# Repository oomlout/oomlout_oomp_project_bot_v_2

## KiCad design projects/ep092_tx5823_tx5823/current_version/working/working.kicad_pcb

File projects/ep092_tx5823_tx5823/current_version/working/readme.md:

# tx5823
 
## summary 
* id: ep092_tx5823_tx5823
* user: ep092
* name: tx5823
* board: tx5823
* repo: https://github.com/ep092/TX5823
* src_file_repo_kicad_pcb: TX5823.kicad_pcb
* src_file_repo_kicad_pcb_link: https://github.com/ep092/TX5823/tree/master/TX5823.kicad_pcb

* src_file_repo_sch: TX5823.sch
* src_file_repo_sch_link: https://github.com/ep092/TX5823/tree/master/TX5823.sch
* full details link: https://github.com/oomlout/oomlout_oomp_project_bot_v_2/tree/main/projects/ep092_tx5823_tx5823/current_version/working

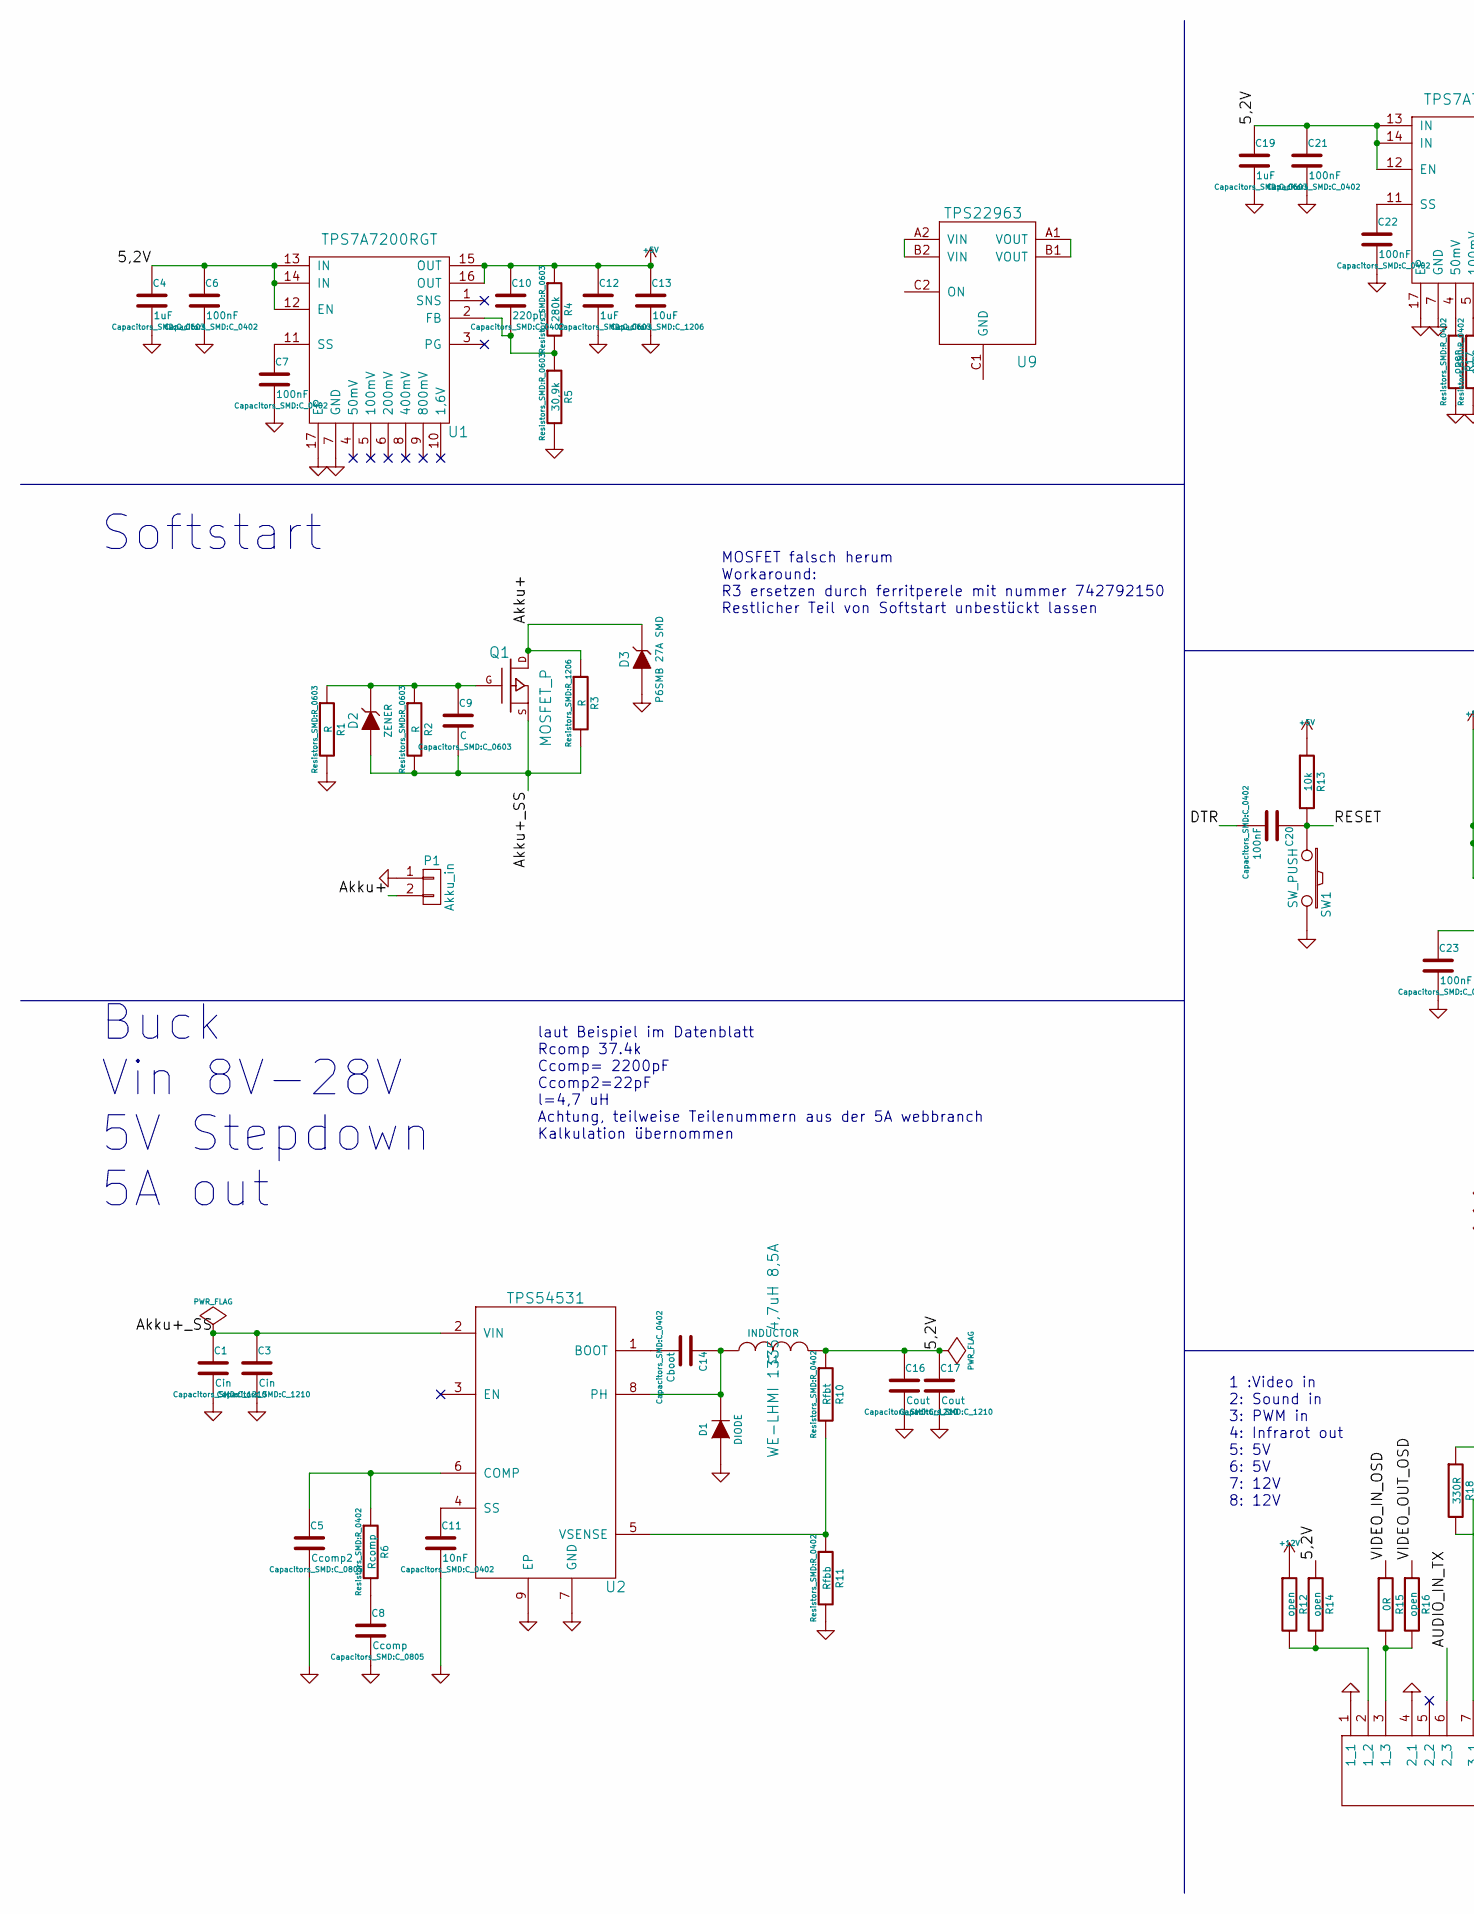
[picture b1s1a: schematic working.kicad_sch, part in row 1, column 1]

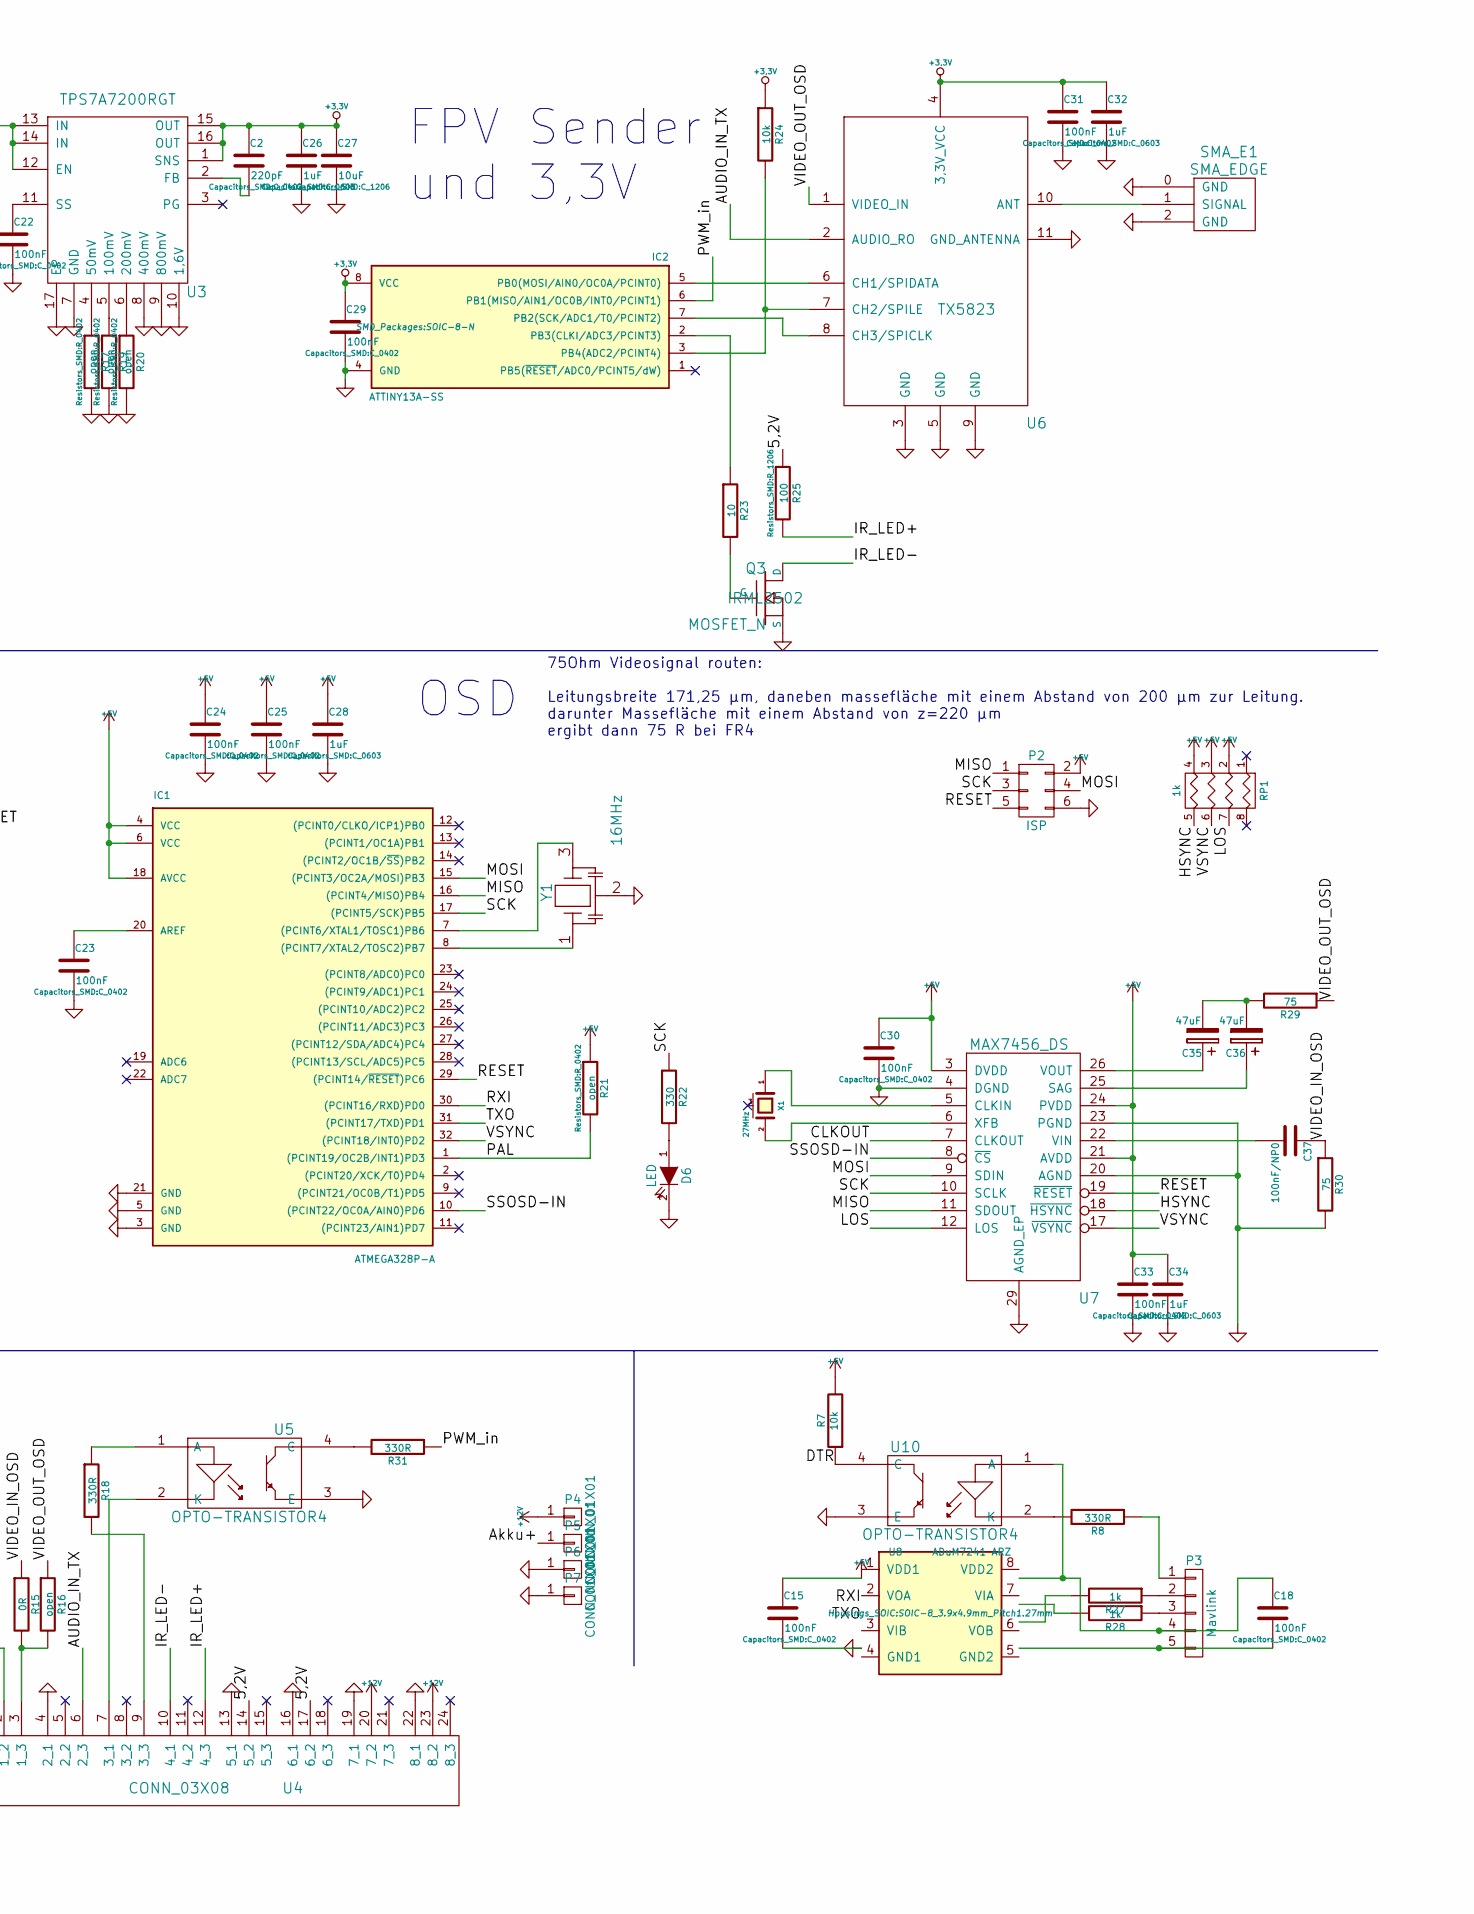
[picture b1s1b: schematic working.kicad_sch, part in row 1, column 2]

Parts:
C1, C3: Cin; C_1210
C2, C10: 220pF; C_0402
C4, C12, C19, C26, C28, C32, C34: 1uF; C_0603
C5: Ccomp2; C_0805
C6, C7, C15, C18, C20, C21, C22, C23, C24, C25, C29, C30, C31, C33: 100nF; C_0402
C8: Ccomp; C_0805
C9: C; C_0603
C11: 10nF; C_0402
C13, C27: 10uF; C_1206
C14: Cboot; C_0402
C16, C17: Cout; C_1210
C35, C36: 47uF; TantalC_SizeB_EIA-3528_Reflow
C37: 100nF/NP0; C_1206
D1: DIODE; POWERDI5
D2: ZENER; Diode-MiniMELF_Standard
D3: P6SMB 27A SMD; Diode-SMB_Standard
D6: LED; LED-0603
IC1: ATMEGA328P-A; TQFP-32_7x7mm_Pitch0.8mm
IC2: ATTINY13A-SS; SOIC-8-N
L1: INDUCTOR; Choke_SMD_Wuerth-WE-PD-Typ-LS_Handsoldering
P1: Akku_in; Socket_Strip_Angled_1x02
P2: ISP; micro_match3x2
P3: Mavlink; Connector_Molex_PicoBlade_53261-0571
P4, P5, P6, P7: CONN_01X01; Pin_Header_Straight_1x01
Q1: MOSFET_P; SO8_WITH_EP
Q3: MOSFET_N; SOT23_GDS
R1, R2: R; R_0603
R3: R; R_1206
R4: 280k; R_0603
R5: 30,9k; R_0603
R6: Rcomp; R_0402
R7, R13, R24: 10k; R_0603
R8: 330R; R_0603
R10: Rfbt; R_0402
R11: Rfbb; R_0402
R12, R14, R16: open; R_0603
R15: 0R; R_0603
R17, R19, R20, R21: open; R_0402
R18: 330R; R_0805
R22: 330; R_0805
R23: 10; R_0805
R25: 100; R_1206
R27, R28: 1k; R_0603
R29, R30: 75; C_0805
R31: 330R; C_0805
RP1: 1k; R_Array_Concave_4x0603
SMA_E1: SMA_EDGE
SW1: SW_PUSH; EVQP7A
U1, U3: TPS7A7200RGT; QFN-16-1EP_3x3mm_Pitch0.5mm
U2: TPS54531; SO8_EP
U4: CONN_03X08; Conn_03x08
U5, U10: OPTO-TRANSISTOR4; SO-4
U6: TX5823
U7: MAX7456_DS; TSSOP-28_4.4x9.7mm_Pitch0.65mm_EP
U8: ADuM7241 ARZ; SOIC-8_3.9x4.9mm_Pitch1.27mm
U9: TPS22963; DSBGS(6)
X1: 27MHz; CRYSTAL_MT
Y1: 16MHz; CerOsc_3,2x1,3

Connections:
+3.3V: C2.1, C26.1, C27.1, C29.1, C31.1, C32.1, IC2.8 (VCC), R24.1, U3.1 (SNS), U3.15 (OUT), U3.16 (OUT), U6.4 (3,3V_VCC)
+5V: C10.1, C12.1, C13.1, C15.1, C24.1, C25.1, C28.1, C30.1, C33.1, C34.1, IC1.4 (VCC), IC1.6 (VCC), IC1.18 (AVCC), P2.2, R4.1, R7.2, R13.1, R21.1, RP1.2, RP1.3, RP1.4, U1.15 (OUT), U1.16 (OUT), U7.3 (DVDD), U7.21 (AVDD), U7.24 (PVDD), U8.1 (VDD1)
+12V: P4.1, R12.1, U4.20 (7_2), U4.23 (8_2)
/5,2V: C4.1, C6.1, C16.1, C17.1, C19.1, C21.1, L1.2, R10.1, R14.1, R25.1, U1.12 (EN), U1.13 (IN), U1.14 (IN), U3.12 (EN), U3.13 (IN), U3.14 (IN), U4.14 (5_2), U4.17 (6_2)
/AUDIO_IN_TX: U4.6 (2_3), U6.2 (AUDIO_RO)
/Akku+: D3.2 (K), P1.2, P5.1, Q1.D, R3.1
/Akku+_SS: C1.1, C3.1, C9.2, D2.1 (A), Q1.S, R2.2, R3.2, U2.2 (VIN)
/CLKOUT: U7.7 (CLKOUT)
/DTR: C20.2, R7.1, U10.4 (C)
/HSYNC: RP1.5 (R4), U7.18 (~HSYNC)
/IR_LED+: R25.2, U4.12 (4_3)
/IR_LED-: Q3.D, U4.10 (4_1)
/LOS: RP1.7 (R2), U7.12 (LOS)
/MISO: IC1.16 ((PCINT4/MISO)PB4), P2.1, U7.11 (SDOUT)
/MOSI: IC1.15 ((PCINT3/OC2A/MOSI)PB3), P2.4, U7.9 (SDIN)
/PAL: IC1.1 ((PCINT19/OC2B/INT1)PD3), R21.2
/PWM_in: IC2.6 (PB1(MISO/AIN1/OC0B/INT0/PCINT1)), R31.1
/RESET: C20.1, IC1.29 ((PCINT14/~RESET)PC6), P2.5, R13.2, SW1.1, U7.19 (~RESET)
/RXI: IC1.30 ((PCINT16/RXD)PD0), U8.2 (VOA)
/SCK: IC1.17 ((PCINT5/SCK)PB5), P2.3, R22.1, U7.10 (SCLK)
/SSOSD-IN: IC1.10 ((PCINT22/OC0A/AIN0)PD6), U7.8 (~CS)
/TXO: IC1.31 ((PCINT17/TXD)PD1), U8.3 (VIB)
/VIDEO_IN_OSD: C37.1, R15.1, R30.1
/VIDEO_OUT_OSD: R16.1, R29.1, U6.1 (VIDEO_IN)
/VSYNC: IC1.32 ((PCINT18/INT0)PD2), RP1.6 (R3), U7.17 (~VSYNC)
GND: C1.2, C3.2, C4.2, C5.2, C6.2, C7.2, C8.2, C11.2, C12.2, C13.2, C15.2, C16.2, C17.2, C19.2, C21.2, C22.2, C23.2, C24.2, C25.2, C26.2, C27.2, C28.2, C29.2, C30.2, C31.2, C32.2, C33.2, C34.2, D1.1 (A), D3.1 (A), D6.2 (K), IC1.3 (GND), IC1.5 (GND), IC1.21 (GND), IC2.4 (GND), P1.1, P2.6, P6.1, P7.1, Q3.S, R1.2, R5.2, R11.2, R17.2, R19.2, R20.2, R30.2, SMA_E1.0 (GND), SMA_E1.2 (GND), SW1.2, U1.7 (GND), U1.17 (EP), U2.7 (GND), U2.9 (EP), U3.7 (GND), U3.8 (400mV), U3.9 (800mV), U3.10 (1,6V), U3.17 (EP), U4.1 (1_1), U4.4 (2_1), U4.13 (5_1), U4.16 (6_1), U4.19 (7_1), U4.22 (8_1), U5.3 (E), U6.3 (GND), U6.5 (GND), U6.9 (GND), U6.11 (GND_ANTENNA), U7.4 (DGND), U7.20 (AGND), U7.23 (PGND), U7.29 (AGND_EP), U8.4 (GND1), U10.3 (E), Y1.2
unnamed: C2.2, U3.2 (FB)
unnamed: C5.1, R6.1, U2.6 (COMP)
unnamed: C7.1, U1.11 (SS)
unnamed: C8.1, R6.2
unnamed: C9.1, D2.2 (K), Q1.G, R1.1, R2.1
unnamed: C10.2, R4.2, R5.1, U1.2 (FB)
unnamed: C11.1, U2.4 (SS)
unnamed: C14.1, D1.2 (K), L1.1, U2.8 (PH)
unnamed: C14.2, U2.1 (BOOT)
unnamed: C22.1, U3.11 (SS)
unnamed: C23.1, IC1.20 (AREF)
unnamed: C35.1, U7.26 (VOUT)
unnamed: C35.2, C36.2, R29.2
unnamed: C36.1, U7.25 (SAG)
unnamed: C37.2, U7.22 (VIN)
unnamed: D6.1 (A), R22.2
unnamed: IC1.7 ((PCINT6/XTAL1/TOSC1)PB6), Y1.3
unnamed: IC1.8 ((PCINT7/XTAL2/TOSC2)PB7), Y1.1
unnamed: IC2.2 (PB3(CLKI/ADC3/PCINT3)), R23.1
unnamed: IC2.3 (PB4(ADC2/PCINT4)), R24.2, U6.7 (CH2/SPILE)
unnamed: IC2.5 (PB0(MOSI/AIN0/OC0A/PCINT0)), U6.6 (CH1/SPIDATA)
unnamed: IC2.7 (PB2(SCK/ADC1/T0/PCINT2)), U6.8 (CH3/SPICLK)
unnamed: P3.1, R8.1
unnamed: P3.2, R27.1
unnamed: P3.3, R28.1
unnamed: Q3.G, R23.2
unnamed: R8.2, U10.2 (K)
unnamed: R10.2, R11.1, U2.5 (VSENSE)
unnamed: R12.2, R14.2, U4.2 (1_2)
unnamed: R15.2, R16.2, U4.3 (1_3)
unnamed: R17.1, U3.4 (50mV)
unnamed: R18.1, U5.1 (A)
unnamed: R18.2, U4.9 (3_3)
unnamed: R19.1, U3.5 (100mV)
unnamed: R20.1, U3.6 (200mV)
unnamed: R27.2, U8.6 (VOB)
unnamed: R28.2, U8.7 (VIA)
unnamed: R31.2, U5.4 (C)
unnamed: SMA_E1.1 (SIGNAL), U6.10 (ANT)
unnamed: U4.7 (3_1), U5.2 (K)
unnamed: U7.5 (CLKIN), X1.1
unnamed: U7.6 (XFB), X1.2
unnamed: U9.A1 (VOUT), U9.B1 (VOUT)
unnamed: U9.A2 (VIN), U9.B2 (VIN)

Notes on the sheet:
OSD
Buck Vin 8V-28V 5V Stepdown 5A out
1 :Video in 2: Sound in 3: PWM in 4: Infrarot out 5: 5V 6: 5V 7: 12V 8: 12V
FPV Sender und 3,3V
laut Beispiel im Datenblatt Rcomp 37.4k Ccomp= 2200pF Ccomp2=22pF l=4,7 uH Achtung, teilweise Teilenummern aus der 5A webbranch Kalkulation übernommen
MOSFET falsch herum Workaround: R3 ersetzen durch ferritperele mit nummer 742792150 Restlicher Teil von Softstart unbestückt lassen
Softstart
75Ohm Videosignal routen: Leitungsbreite 171,25 µm, daneben massefläche mit einem Abstand von 200 µm zur Leitung. darunter Massefläche mit einem Abstand von z=220 µm ergibt dann 75 R bei FR4

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
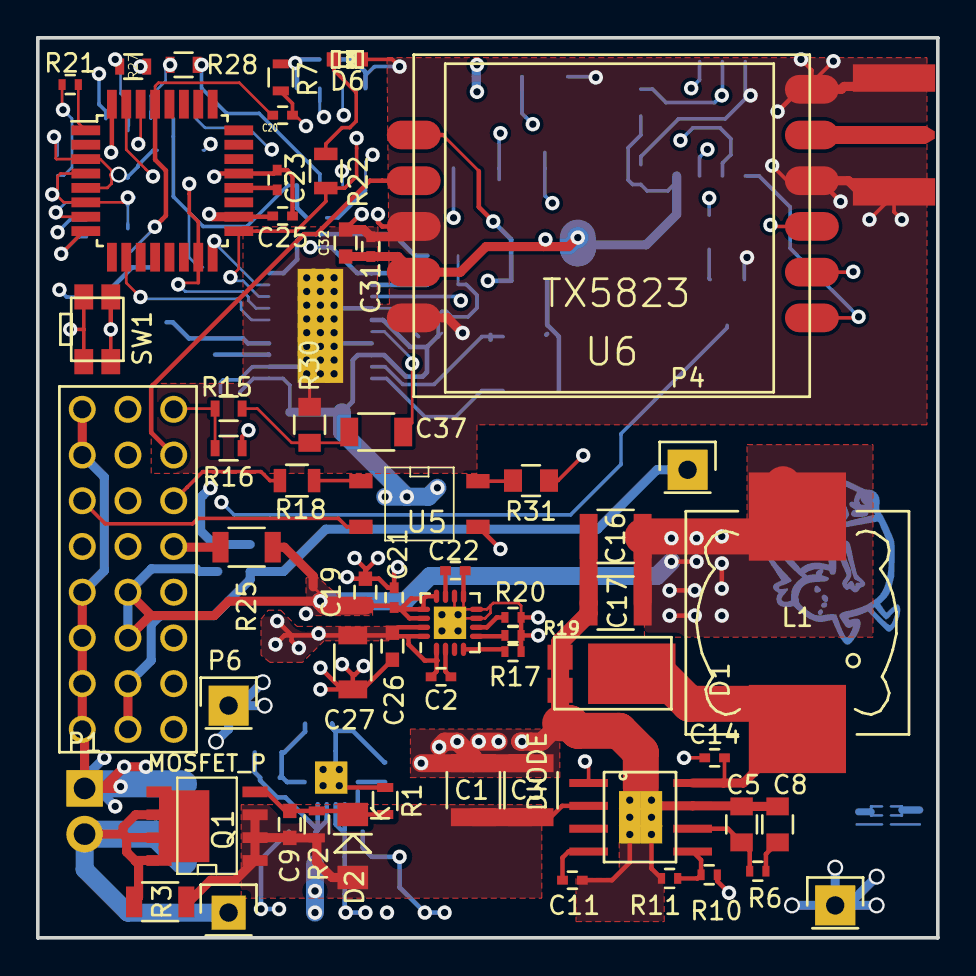
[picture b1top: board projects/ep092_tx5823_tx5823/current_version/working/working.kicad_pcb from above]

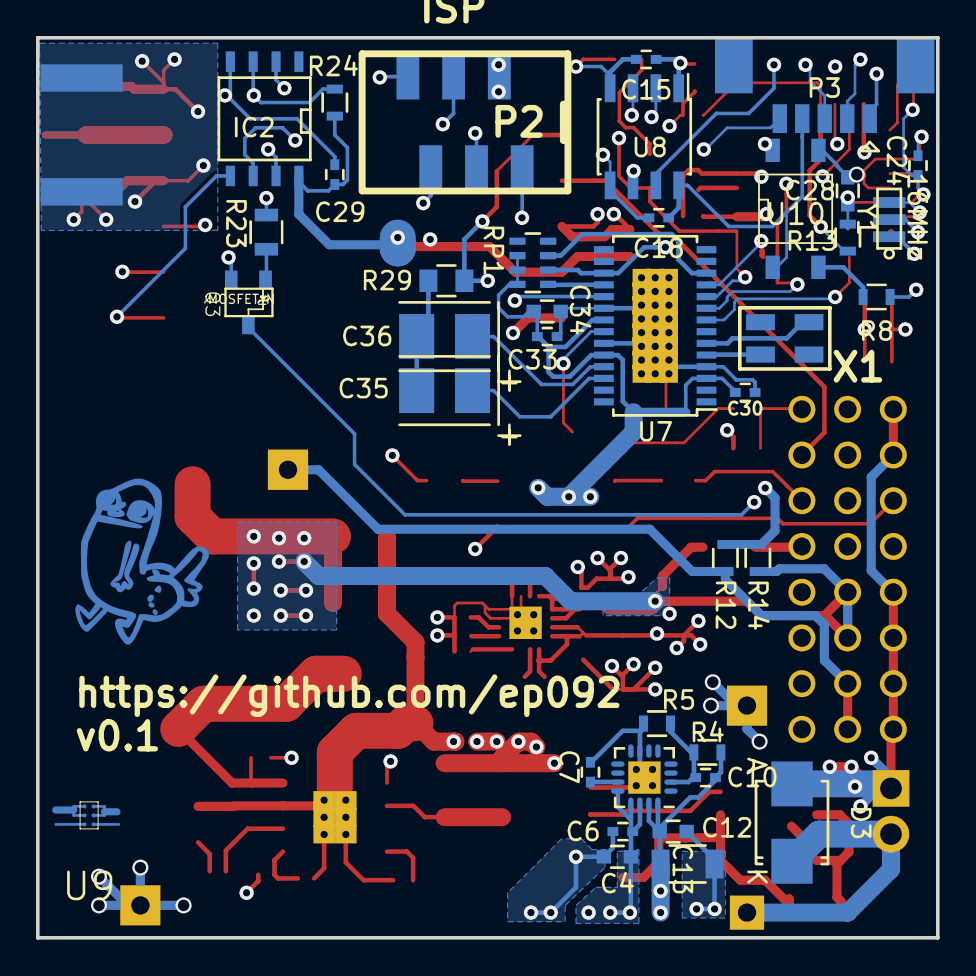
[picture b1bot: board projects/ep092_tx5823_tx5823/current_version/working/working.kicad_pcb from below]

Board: 4 copper layers, 50.0 x 50.0 mm, 97 parts (38 on the bottom side), 71 nets.

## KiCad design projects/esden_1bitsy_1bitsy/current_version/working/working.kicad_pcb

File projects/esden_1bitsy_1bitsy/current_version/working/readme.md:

# 1bitsy
 
## summary 
* id: esden_1bitsy_1bitsy
* user: esden
* name: 1bitsy
* board: 1bitsy
* repo: https://github.com/esden/1BitSy
* src_file_repo_kicad_pcb: 1bitsy/v1.0d/1bitsy-rr.kicad_pcb
* src_file_repo_kicad_pcb_link: https://github.com/esden/1BitSy/tree/master/1bitsy/v1.0d/1bitsy-rr.kicad_pcb

* src_file_repo_sch: 1bitsy/v1.0c/1bitsy.sch
* src_file_repo_sch_link: https://github.com/esden/1BitSy/tree/master/1bitsy/v1.0c/1bitsy.sch
* full details link: https://github.com/oomlout/oomlout_oomp_project_bot_v_2/tree/main/projects/esden_1bitsy_1bitsy/current_version/working

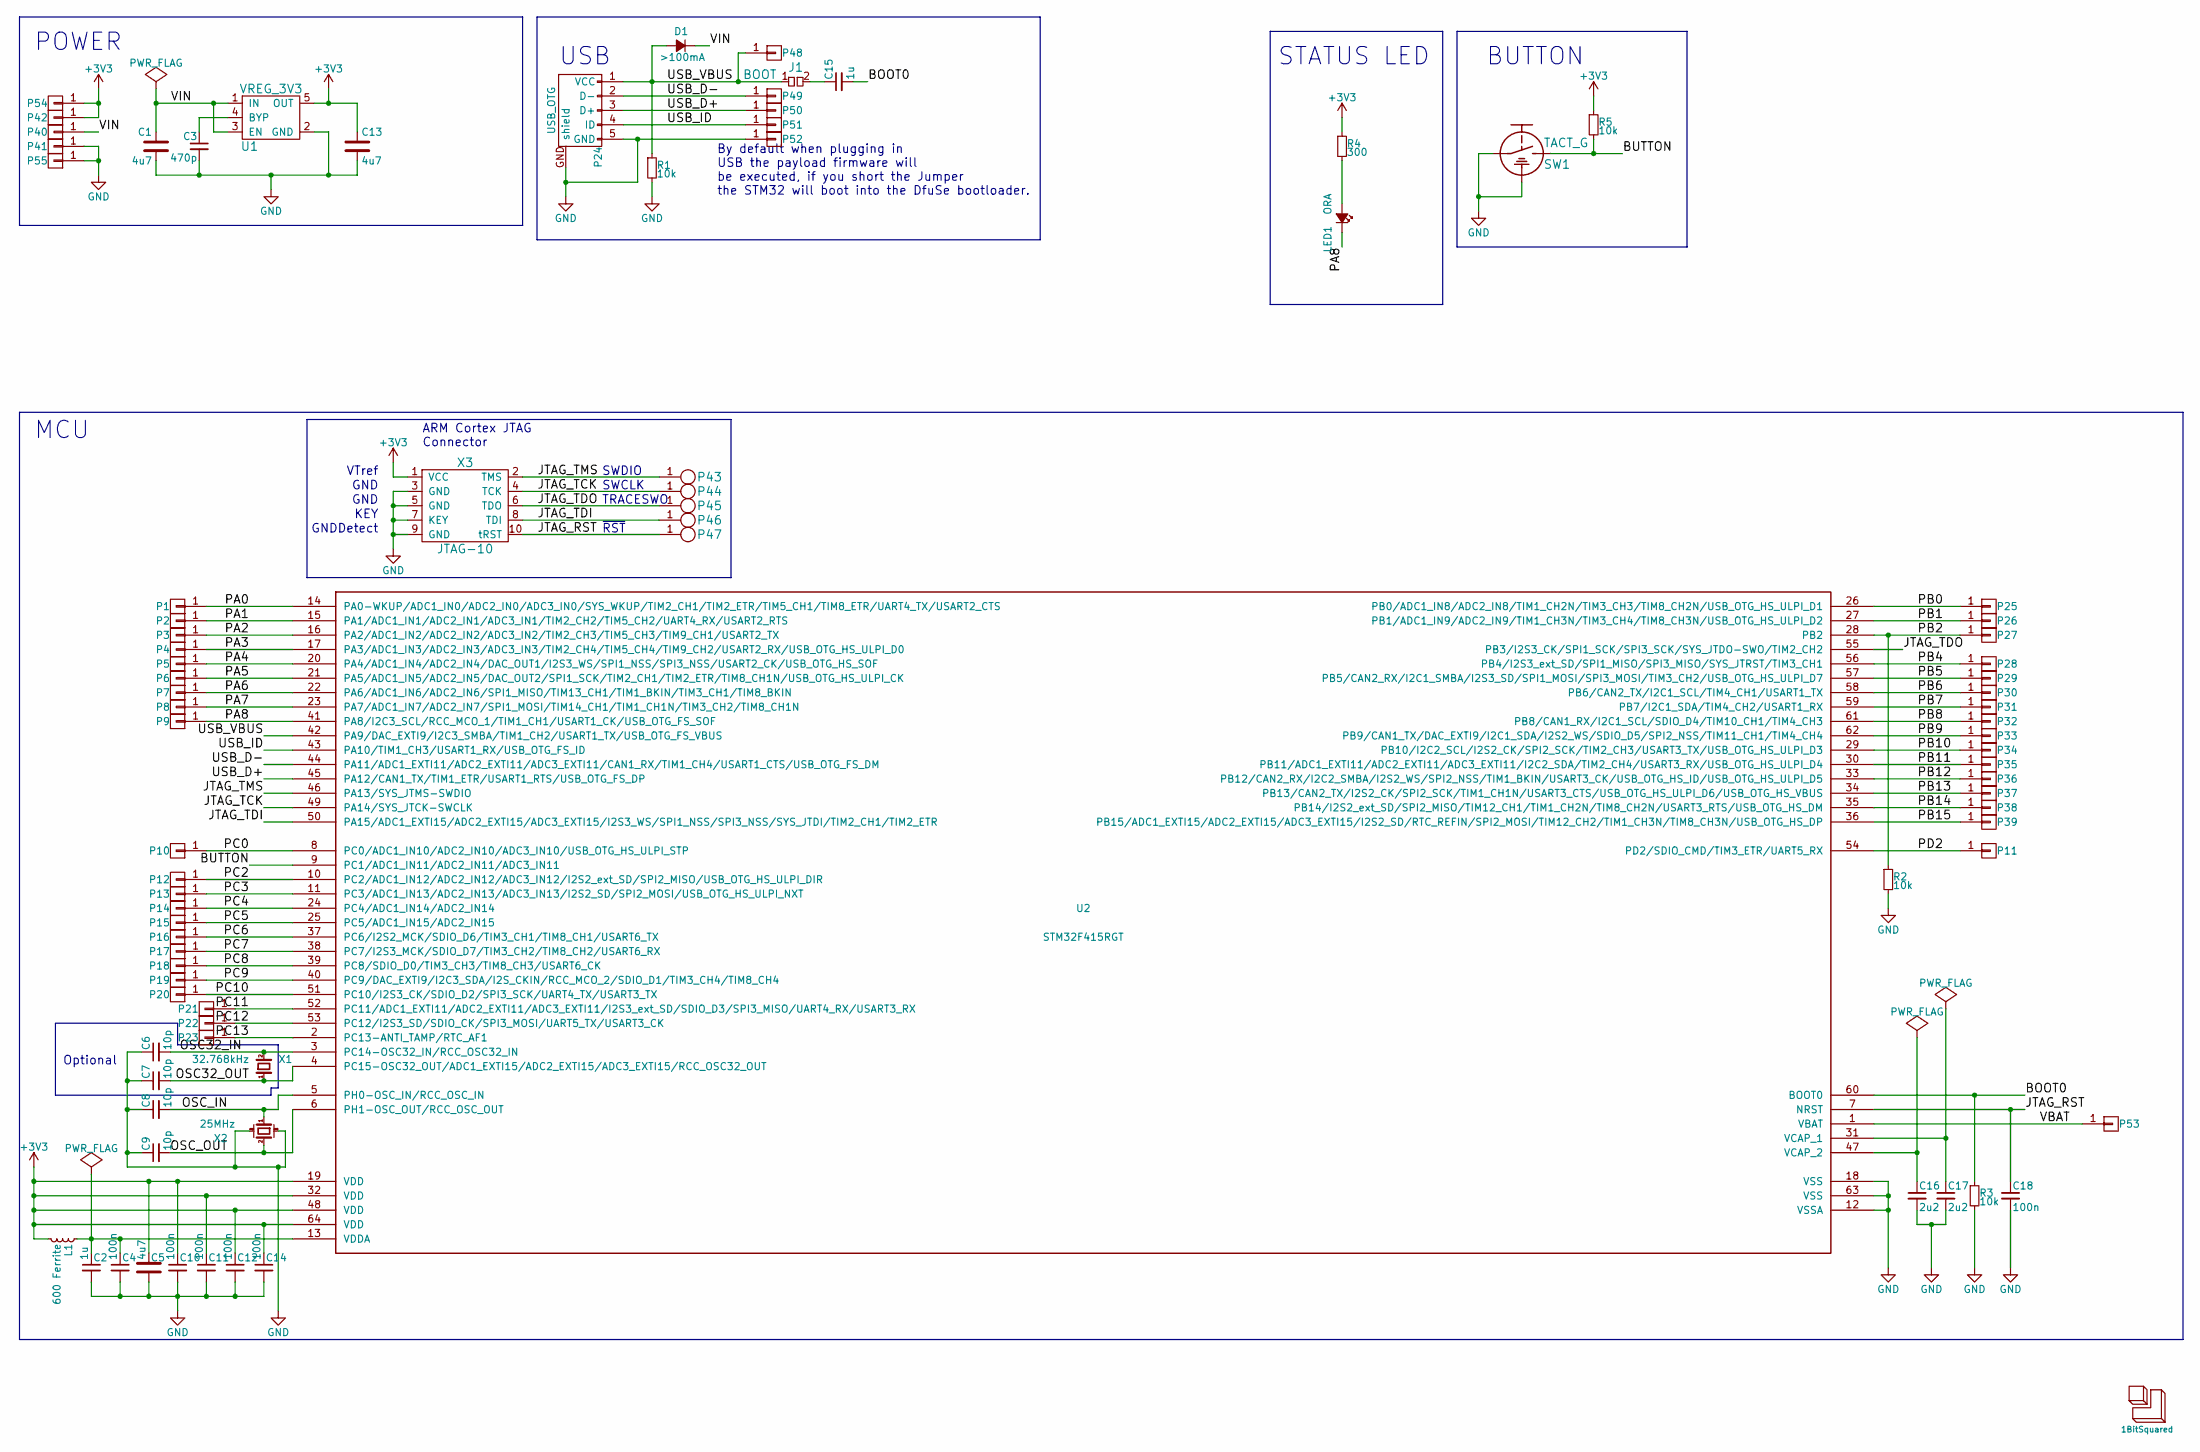
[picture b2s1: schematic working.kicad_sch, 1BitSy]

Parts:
C1, C5, C13: 4u7; C_0603
C2, C15: 1u; C_0402
C3: 470p; C_0402
C4, C10, C11, C12, C14, C18: 100n; C_0402
C6, C7: 10p; C_0603
C8, C9: 10p; C_0402
C16, C17: 2u2; C_0402
D1: >100mA; D_0603
J1: BOOT; J_0603
L1: 600 Ferrite; L_0402
LED1: ORA; D_0603
LOGO1: 1BitSquared; 1b2_Logo_SilkS_7.5mm
P1, P2, P3, P4, P5, P6, P7, P8, P9, P10, P11, P12, P13, P14, P15, P16, P17, P18, P19, P20, P21, P22, P23, P25, P26, P27, P28, P29, P30, P31, P32, P33, P34, P35, P36, P37, P38, P39, P40, P41, P42, P53, P54, P55: CONN_01X01; Pin_Header_Straight_Round_1x01
P24: USB_OTG; Connector_USB_Micro_B_SMD
P43, P44, P45, P46, P47: TP; POGO_PAD_SMD_R_1x1
P48, P49, P50, P51, P52: CONN_01X01; PAD_SMD_1x2.65
R1, R2, R3, R5: 10k; R_0402
R4: 300; R_0402
SW1: TACT_G; Tact_Switch_Top_B3U-1000P
U1: VREG_3V3; SOT-23-5
U2: STM32F415RGT; LQFP-64_10x10mm_Pitch0.5mm
X1: 32.768kHz; ABS07
X2: 25MHz; ABM8
X3: JTAG-10; FTSH-105-XX-X-DV

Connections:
+3V3: C5.1, C10.1, C11.1, C12.1, C13.1, C14.1, L1.1, P42.1, P54.1, R4.1, R5.1, U1.5 (OUT), U2.19 (VDD), U2.32 (VDD), U2.48 (VDD), U2.64 (VDD), X3.1 (VCC)
/BOOT0: C15.2, R3.1, U2.60 (BOOT0)
/BUTTON: R5.2, SW1.2, U2.9 (PC1/ADC1_IN11/ADC2_IN11/ADC3_IN11)
/JTAG_RST: C18.1, P47.1, U2.7 (NRST), X3.10 (tRST)
/JTAG_TCK: P44.1, U2.49 (PA14/SYS_JTCK-SWCLK), X3.4 (TCK)
/JTAG_TDI: P46.1, U2.50 (PA15/ADC1_EXTI15/ADC2_EXTI15/ADC3_EXTI1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), X3.8 (TDI)
/JTAG_TDO: P45.1, U2.55 (PB3/I2S3_CK/SPI1_SCK/SPI3_SCK/SYS_JTDO-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), X3.6 (TDO)
/JTAG_TMS: P43.1, U2.46 (PA13/SYS_JTMS-SWDIO), X3.2 (TMS)
/OSC32_IN: C6.2, U2.3 (PC14-OSC32_IN/RCC_OSC32_IN), X1.2
/OSC32_OUT: C7.2, U2.4 (PC15-OSC32_OUT/ADC1_EXTI15/ADC2_EXTI15/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), X1.1
/OSC_IN: C8.2, U2.5 (PH0-OSC_IN/RCC_OSC_IN), X2.1
/OSC_OUT: C9.2, U2.6 (PH1-OSC_OUT/RCC_OSC_OUT), X2.2
/PA0: P1.1, U2.14 (PA0-WKUP/ADC1_IN0/ADC2_IN0/ADC3_IN0/SYS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)
/PA1: P2.1, U2.15 (PA1/ADC1_IN1/ADC2_IN1/ADC3_IN1/TIM2_CH2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)
/PA2: P3.1, U2.16 (PA2/ADC1_IN2/ADC2_IN2/ADC3_IN2/TIM2_CH3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)
/PA3: P4.1, U2.17 (PA3/ADC1_IN3/ADC2_IN3/ADC3_IN3/TIM2_CH4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)
/PA4: P5.1, U2.20 (PA4/ADC1_IN4/ADC2_IN4/DAC_OUT1/I2S3_WS/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)
/PA5: P6.1, U2.21 (PA5/ADC1_IN5/ADC2_IN5/DAC_OUT2/SPI1_SCK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)
/PA6: P7.1, U2.22 (PA6/ADC1_IN6/ADC2_IN6/SPI1_MISO/TIM13_C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)
/PA7: P8.1, U2.23 (PA7/ADC1_IN7/ADC2_IN7/SPI1_MOSI/TIM14_C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)
/PA8: LED1.C, P9.1, U2.41 (PA8/I2C3_SCL/RCC_MCO_1/TIM1_CH1/USART1_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)
/PB0: P25.1, U2.26 (PB0/ADC1_IN8/ADC2_IN8/TIM1_CH2N/TIM3_CH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)
/PB1: P26.1, U2.27 (PB1/ADC1_IN9/ADC2_IN9/TIM1_CH3N/TIM3_CH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)
/PB2: P27.1, R2.1, U2.28 (PB2)
/PB4: P28.1, U2.56 (PB4/I2S3_ext_SD/SPI1_MISO/SPI3_MISO/SYS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)
/PB5: P29.1, U2.57 (PB5/CAN2_RX/I2C1_SMBA/I2S3_SD/SPI1_MOSI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)
/PB6: P30.1, U2.58 (PB6/CAN2_TX/I2C1_SCL/TIM4_CH1/USART1_TX)
/PB7: P31.1, U2.59 (PB7/I2C1_SDA/TIM4_CH2/USART1_RX)
/PB8: P32.1, U2.61 (PB8/CAN1_RX/I2C1_SCL/SDIO_D4/TIM10_CH1/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)
/PB9: P33.1, U2.62 (PB9/CAN1_TX/DAC_EXTI9/I2C1_SDA/I2S2_WS/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)
/PB10: P34.1, U2.29 (PB10/I2C2_SCL/I2S2_CK/SPI2_SCK/TIM2_CH3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)
/PB11: P35.1, U2.30 (PB11/ADC1_EXTI11/ADC2_EXTI11/ADC3_EXTI1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)
/PB12: P36.1, U2.33 (PB12/CAN2_RX/I2C2_SMBA/I2S2_WS/SPI2_NSS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)
/PB13: P37.1, U2.34 (PB13/CAN2_TX/I2S2_CK/SPI2_SCK/TIM1_CH1N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)
/PB14: P38.1, U2.35 (PB14/I2S2_ext_SD/SPI2_MISO/TIM12_CH1/TI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)
/PB15: P39.1, U2.36 (PB15/ADC1_EXTI15/ADC2_EXTI15/ADC3_EXTI1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)
/PC0: P10.1, U2.8 (PC0/ADC1_IN10/ADC2_IN10/ADC3_IN10/USB_O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)
/PC2: P12.1, U2.10 (PC2/ADC1_IN12/ADC2_IN12/ADC3_IN12/I2S2_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)
/PC3: P13.1, U2.11 (PC3/ADC1_IN13/ADC2_IN13/ADC3_IN13/I2S2_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)
/PC4: P14.1, U2.24 (PC4/ADC1_IN14/ADC2_IN14)
/PC5: P15.1, U2.25 (PC5/ADC1_IN15/ADC2_IN15)
/PC6: P16.1, U2.37 (PC6/I2S2_MCK/SDIO_D6/TIM3_CH1/TIM8_CH1/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)
/PC7: P17.1, U2.38 (PC7/I2S3_MCK/SDIO_D7/TIM3_CH2/TIM8_CH2/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)
/PC8: P18.1, U2.39 (PC8/SDIO_D0/TIM3_CH3/TIM8_CH3/USART6_CK)
/PC9: P19.1, U2.40 (PC9/DAC_EXTI9/I2C3_SDA/I2S_CKIN/RCC_MCO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)
/PC10: P20.1, U2.51 (PC10/I2S3_CK/SDIO_D2/SPI3_SCK/UART4_TX/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)
/PC11: P21.1, U2.52 (PC11/ADC1_EXTI11/ADC2_EXTI11/ADC3_EXTI1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)
/PC12: P22.1, U2.53 (PC12/I2S3_SD/SDIO_CK/SPI3_MOSI/UART5_TX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)
/PC13: P23.1, U2.2 (PC13-ANTI_TAMP/RTC_AF1)
/PD2: P11.1, U2.54 (PD2/SDIO_CMD/TIM3_ETR/UART5_RX)
/USB_D+: P24.3 (D+), P50.1, U2.45 (PA12/CAN1_TX/TIM1_ETR/USART1_RTS/USB_OT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)
/USB_D-: P24.2 (D-), P49.1, U2.44 (PA11/ADC1_EXTI11/ADC2_EXTI11/ADC3_EXTI1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)
/USB_ID: P24.4 (ID), P51.1, U2.43 (PA10/TIM1_CH3/USART1_RX/USB_OTG_FS_ID)
/USB_VBUS: D1.A, J1.1, P24.1 (VCC), P48.1, R1.1, U2.42 (PA9/DAC_EXTI9/I2C3_SMBA/TIM1_CH2/USART1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)
/VBAT: P53.1, U2.1 (VBAT)
/VIN: C1.1, D1.C, P40.1, U1.1 (IN), U1.3 (EN)
GND: C1.2, C2.2, C3.2, C4.2, C5.2, C6.1, C7.1, C8.1, C9.1, C10.2, C11.2, C12.2, C13.2, C14.2, C16.2, C17.2, C18.2, P24.5 (GND), P24.GND (shield), P41.1, P52.1, P55.1, R1.2, R2.2, R3.2, SW1.1, SW1.GND (case), U1.2 (GND), U2.12 (VSSA), U2.18 (VSS), U2.63 (VSS), X2.GND (case), X3.3 (GND), X3.5 (GND), X3.7 (KEY), X3.9 (GND)
unnamed: C2.1, C4.1, L1.2, U2.13 (VDDA)
unnamed: C3.1, U1.4 (BYP)
unnamed: C15.1, J1.2
unnamed: C16.1, U2.47 (VCAP_2)
unnamed: C17.1, U2.31 (VCAP_1)
unnamed: LED1.A, R4.2

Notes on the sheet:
SWCLK
POWER
BUTTON
GND
TRACESWO
USB
By default when plugging in USB the payload firmware will be executed, if you short the Jumper the STM32 will boot into the DfuSe bootloader.
GNDDetect
STATUS LED
MCU
Optional
SWDIO
~{RST}
ARM Cortex JTAG Connector
KEY
VTref

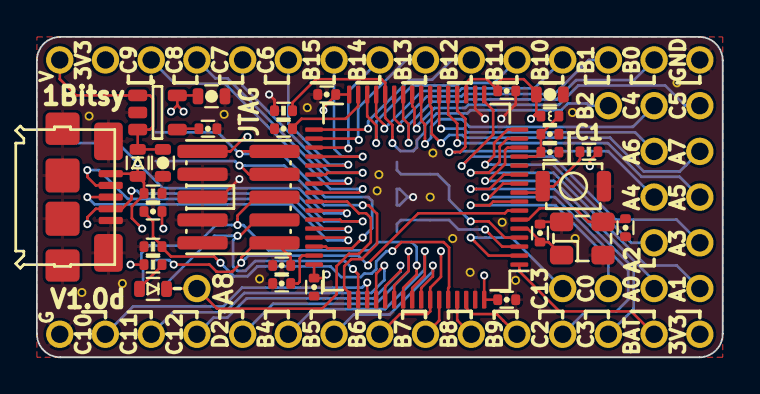
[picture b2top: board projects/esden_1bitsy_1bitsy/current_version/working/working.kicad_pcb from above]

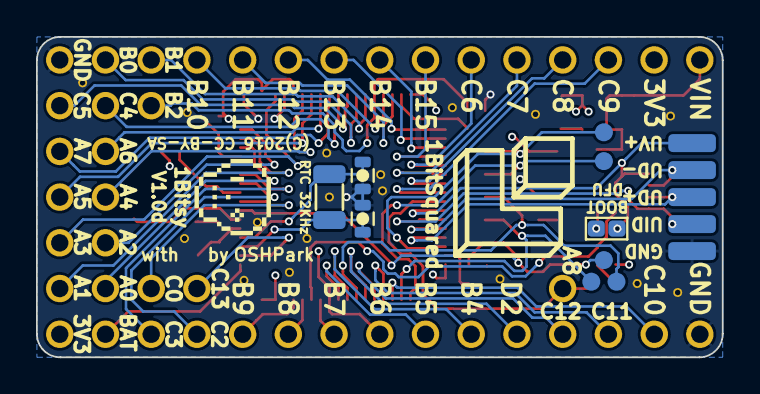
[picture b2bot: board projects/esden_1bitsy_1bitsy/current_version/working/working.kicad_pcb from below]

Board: 4 copper layers, 38.1 x 17.8 mm, 88 parts (14 on the bottom side), 63 nets.

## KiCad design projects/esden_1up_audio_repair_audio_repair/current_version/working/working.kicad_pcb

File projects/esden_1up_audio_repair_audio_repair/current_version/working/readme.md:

# 1up_audio_repair
 
## summary 
* id: esden_1up_audio_repair_audio_repair
* user: esden
* name: 1up_audio_repair
* board: audio_repair
* repo: https://github.com/esden/1up-audio-repair
* src_file_repo_kicad_pcb: v0.3/audio-repair/audio-repair.kicad_pcb
* src_file_repo_kicad_pcb_link: https://github.com/esden/1up-audio-repair/tree/master/v0.3/audio-repair/audio-repair.kicad_pcb

* src_file_repo_sch: v0.3/audio-repair/audio-repair.sch
* src_file_repo_sch_link: https://github.com/esden/1up-audio-repair/tree/master/v0.3/audio-repair/audio-repair.sch
* full details link: https://github.com/oomlout/oomlout_oomp_project_bot_v_2/tree/main/projects/esden_1up_audio_repair_audio_repair/current_version/working

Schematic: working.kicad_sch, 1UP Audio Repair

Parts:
C1: 10µF; C_0603
C2, C3, C4, C11: 100nF; C_0603
C5: 10nF; C_0603
C6: 1µF; C_0603
C7, C8: 220nF; C_0603
C9, C10: 220µF; C_1210
J1: Vin; Pin_Header_Straight_1x01_Pitch2.54mm
J2: Switchcraft_35RAPC4BHN3
J4: Left; Pin_Header_Straight_1x02_Pitch2.54mm
J6: Right; Pin_Header_Straight_1x02_Pitch2.54mm
R1: 100K; R_0603
R2: 680K; R_0603
R3: 1M; R_0603
R6, R8: 33K; R_0603
R7: 18K; R_0603
R9: 51K; R_0603
R10: 10K; R_0603
RV1: 50K; Potentiometer_Bourns_3352T
U1: PAM8019KGR; QFN-20-1EP_4x4mm_Pitch0.5mm
U2: 1bitsy-basic-stubby; 1bitsy-stub

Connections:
+3V3: U2.15 (+3V3)
/DAC_L: C7.2, U2.35 (PA4/ADC4/DAC1/SPI1NSS/SPI3NSS/I2S3WS/US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)
/DAC_R: C8.2, U2.36 (PA5/ADC5/DAC2/T2C1ETR/T8C1N/SPI1SCK/ULP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)
/MUTE: U1.9 (Mute), U2.33 (PA2/ADC2/T2C3/T5C3/T9C1/USART2TX)
/TIP_SW: C11.1, R9.2, U1.10 (HP/~SPK), U2.31 (PA0-WKUP/ADC0/T2C1ETR/T5C1/T8ETR/USART2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)
/VOL_ADC: C5.1, R2.2, R3.1, U2.32 (PA1/ADC1/T2C2/T5C2/USART2RTS/UART4RX)
/~SHUTDOWN: U1.3 (~SD), U2.34 (PA3/ADC3/T2C4/T5C4/T9C2/USART2RX/ULPID0)
GND: C1.2, C2.2, C3.2, C4.2, C5.2, C6.2, C11.2, J2.1, R3.2, R8.2, R10.1, RV1.1, U1.6 (GND), U1.11 (PL), U1.18 (GND), U1.21 (PAD), U2.16 (GND)
unnamed: C6.1, U1.4 (Bypass)
unnamed: C7.1, U1.7 (Lin)
unnamed: C8.1, U1.5 (Rin)
unnamed: C9.1, U1.14 (HPLout)
unnamed: C9.2, J2.5, R10.2
unnamed: C10.1, U1.2 (HPRout)
unnamed: C10.2, J2.2
unnamed: J2.4, R1.2, R9.1
unnamed: J4.1, U1.17 (LoutP)
unnamed: J4.2, U1.15 (LoutN)
unnamed: J6.1, U1.19 (RoutP)
unnamed: J6.2, U1.1 (RoutN)
unnamed: R2.1, RV1.2, U1.8 (Volume)
unnamed: R6.1, R7.2, R8.1
unnamed: R6.2, U1.12 (UVP)
VDD: C1.1, C2.1, C3.1, C4.1, J1.1, R1.1, R7.1, RV1.3, U1.13 (VDD), U1.16 (VDD), U1.20 (VDD)

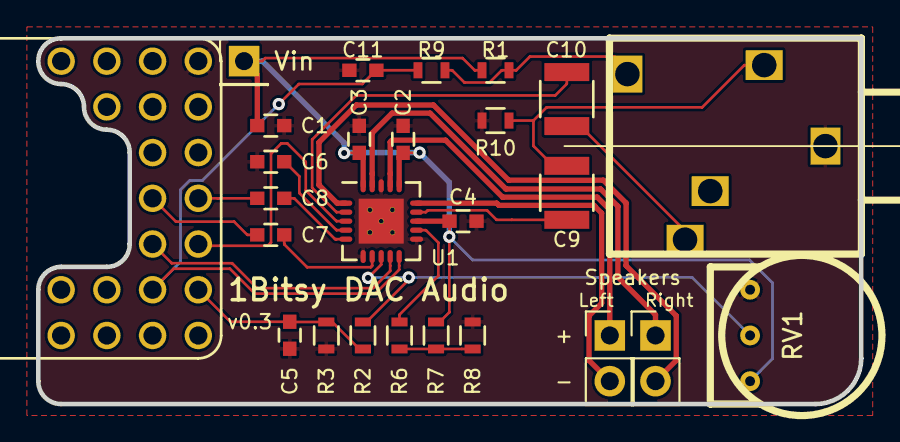
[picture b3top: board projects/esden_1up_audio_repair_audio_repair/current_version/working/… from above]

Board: 2 copper layers, 45.7 x 20.3 mm, 26 parts (0 on the bottom side), 23 nets.

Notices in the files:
projects/esden_1bitsy_1bitsy/current_version/working/working.kicad_pcb:
(C) 2016 Piotr Esden-Tempski
(C) 2016 1BitSquared LLC
License: CC-BY-SA V4.0
(C)2016 CC-BY-SA
projects/esden_bitmagic_bitmagic_basic/current_version/working/working.kicad_pcb:
CC-BY-SA V4.0
(C) 2019 1BitSquared
(C) 2019 Piotr Esden-Tempski
CC-BY-SA 4.0
projects/esden_bitmagic_bitmagic_basic/current_version/working/working.kicad_sch:
(C) 2019-2020 1BitSquared
(C) 2019-2020 Piotr Esden-Tempski
projects/esden_ftdi_multitool_ftdi/current_version/working/working.kicad_pcb:
(C) 2018 Piotr Esden-Tempski
(C) 2018 1BitSquared
